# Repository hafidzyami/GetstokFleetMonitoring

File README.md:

# Tugas Akhir - Getstok Fleet Monitoring

Welcome to the **Getstok Fleet Monitoring** repository! This repository contains three main components: **Frontend**, **Backend**, and **Firmware**, each designed to work together seamlessly. Below are the details of each component.

---

## Table of Contents
- [Frontend](#frontend)
- [Backend](#backend)
- [Firmware](#firmware)
- [Setup](#setup)
  - [Frontend Setup](#frontend-setup)
  - [Backend Setup](#backend-setup)
  - [Firmware Setup](#firmware-setup)
- [License](#license)
- [Contributing](#contributing)

---

## Frontend

The **Frontend** is built using [Next.js](https://nextjs.org/), a React framework for server-rendered and statically generated web applications.

### Features
- Modern UI built with React and Next.js.
- Server-side rendering and API routes for efficient data fetching.
- Optimized performance and SEO.

---

# Backend - Getstok Fleet Monitoring

The backend for Getstok Fleet Monitoring is built with Go (Golang), using the GoFiber framework and GORM for database operations. It follows a clean n-tier architecture and provides RESTful API endpoints with authentication and role-based access control.

## Features

- **Authentication System**: Secure JWT-based authentication with roles (management, planner, driver)
- **RESTful API**: Clean API design following Google JSON Style Guide
- **Documentation**: Integrated Swagger API documentation
- **Database**: PostgreSQL integration with GORM
- **Docker Support**: Containerized development and production environments

## Tech Stack

- **Language**: Go 1.20+
- **Framework**: GoFiber v2
- **ORM**: GORM with PostgreSQL driver
- **Authentication**: JWT (JSON Web Tokens)
- **Documentation**: Swagger/OpenAPI
- **Containerization**: Docker & Docker Compose

## Project Structure

```
backend/
├── config/            # Configuration and database setup
├── controller/        # HTTP request handlers
├── docs/              # Swagger documentation
├── middleware/        # Middleware components (auth, logging, etc.)
├── model/             # Data models and DTOs
├── repository/        # Database access layer
├── service/           # Business logic
├── util/              # Utility functions
├── .env               # Environment variables (not in git)
├── .env.db            # Database environment variables (not in git)
├── .env.example       # Example environment variables
├── .env.db.example    # Example database environment variables
├── Dockerfile         # Multi-stage build for dev and prod
├── docker-compose.yml # Docker Compose configuration
├── go.mod             # Go modules
├── go.sum             # Dependencies lockfile
└── main.go            # Application entry point
```

## Environment Setup

### Prerequisites

- Go 1.20 or higher
- Docker and Docker Compose
- PostgreSQL (if not using Docker)

### Environment Variables

Two environment files are required:

1. `.env` - Application configuration:
```
DB_HOST=postgres
DB_PORT=5432
DB_USER=username
DB_PASSWORD=password
DB_NAME=getstok
DB_DRIVER=postgres
JWT_SECRET=your_secret_key
PORT=8080
```

2. `.env.db` - Database configuration:
```
POSTGRES_USER=username
POSTGRES_PASSWORD=password
POSTGRES_DB=getstok
```

Copy the example files and adjust as needed:
```bash
cp .env.example .env
cp .env.db.example .env.db
```

## Docker Setup

### Running with Docker

```bash
# Build and run containers
docker-compose up --build

# Run in background
docker-compose up -d

# View logs
docker-compose logs -f api
```

### Stopping Containers

```bash
# Stop and remove containers
docker-compose down
```

## Local Setup (Without Docker)

If you prefer to run the application locally:

1. Ensure PostgreSQL is running and accessible
2. Configure `.env` with your database connection details
3. Run the application:

```bash
# Get dependencies
go mod tidy

# Run the application
go run main.go
```

## API Documentation

The API documentation is available through Swagger UI when the application is running:

- Local: http://localhost:8080/swagger/index.html
- Production: https://your-api-domain.com/swagger/index.html

## Authentication

The API uses JWT tokens for authentication. Most endpoints require authentication and some are restricted by role.

### Available Roles

- `management`: Can register users and access all features
- `planner`: Can plan routes and manage fleet operations
- `driver`: Can view assigned routes and update status

### Authentication Flow

1. Register (Management only): `POST /api/auth/register`
2. Login: `POST /api/auth/login`
3. Use the returned token in the Authorization header: `Bearer <token>`

## Development

### Generating Swagger Documentation

```bash
# Install swag if not already installed
go install github.com/swaggo/swag/cmd/swag@latest

# Generate documentation
swag init -g main.go --output docs
```

### Database Migrations

Database migrations are handled automatically by GORM when the application starts.

## Contributing

1. Fork the repository
2. Create your feature branch (`git checkout -b feature/amazing-feature`)
3. Commit your changes (`git commit -m 'Add some amazing feature'`)
4. Push to the branch (`git push origin feature/amazing-feature`)
5. Open a Pull Request

---

## Firmware

The **Firmware** is written in **C++** to control hardware devices efficiently.

### Features
- Optimized for resource-constrained environments.
- Compatible with a variety of microcontrollers.
- Includes communication protocols for interacting with the backend.

---

## Setup

```yaml
frontend:
  steps:
    - navigate: "cd frontend"
    - install_dependencies: "npm install"
    - run_development_server: "npm run dev"
    - open_browser: "http://localhost:3000"

backend:
  steps:
    - navigate: "cd backend"
    - initialize_modules: "go mod tidy"
    - run_application: "go run cmd/main.go"
    - api_url: "http://localhost:8080"

firmware:
  steps:
    - navigate: "cd firmware"
    - open_project: "Open the project in PlatformIO"
    - build_project: "Use the 'Build' button in PlatformIO"
    - upload_firmware: "Use the 'Upload' button to flash the microcontroller"

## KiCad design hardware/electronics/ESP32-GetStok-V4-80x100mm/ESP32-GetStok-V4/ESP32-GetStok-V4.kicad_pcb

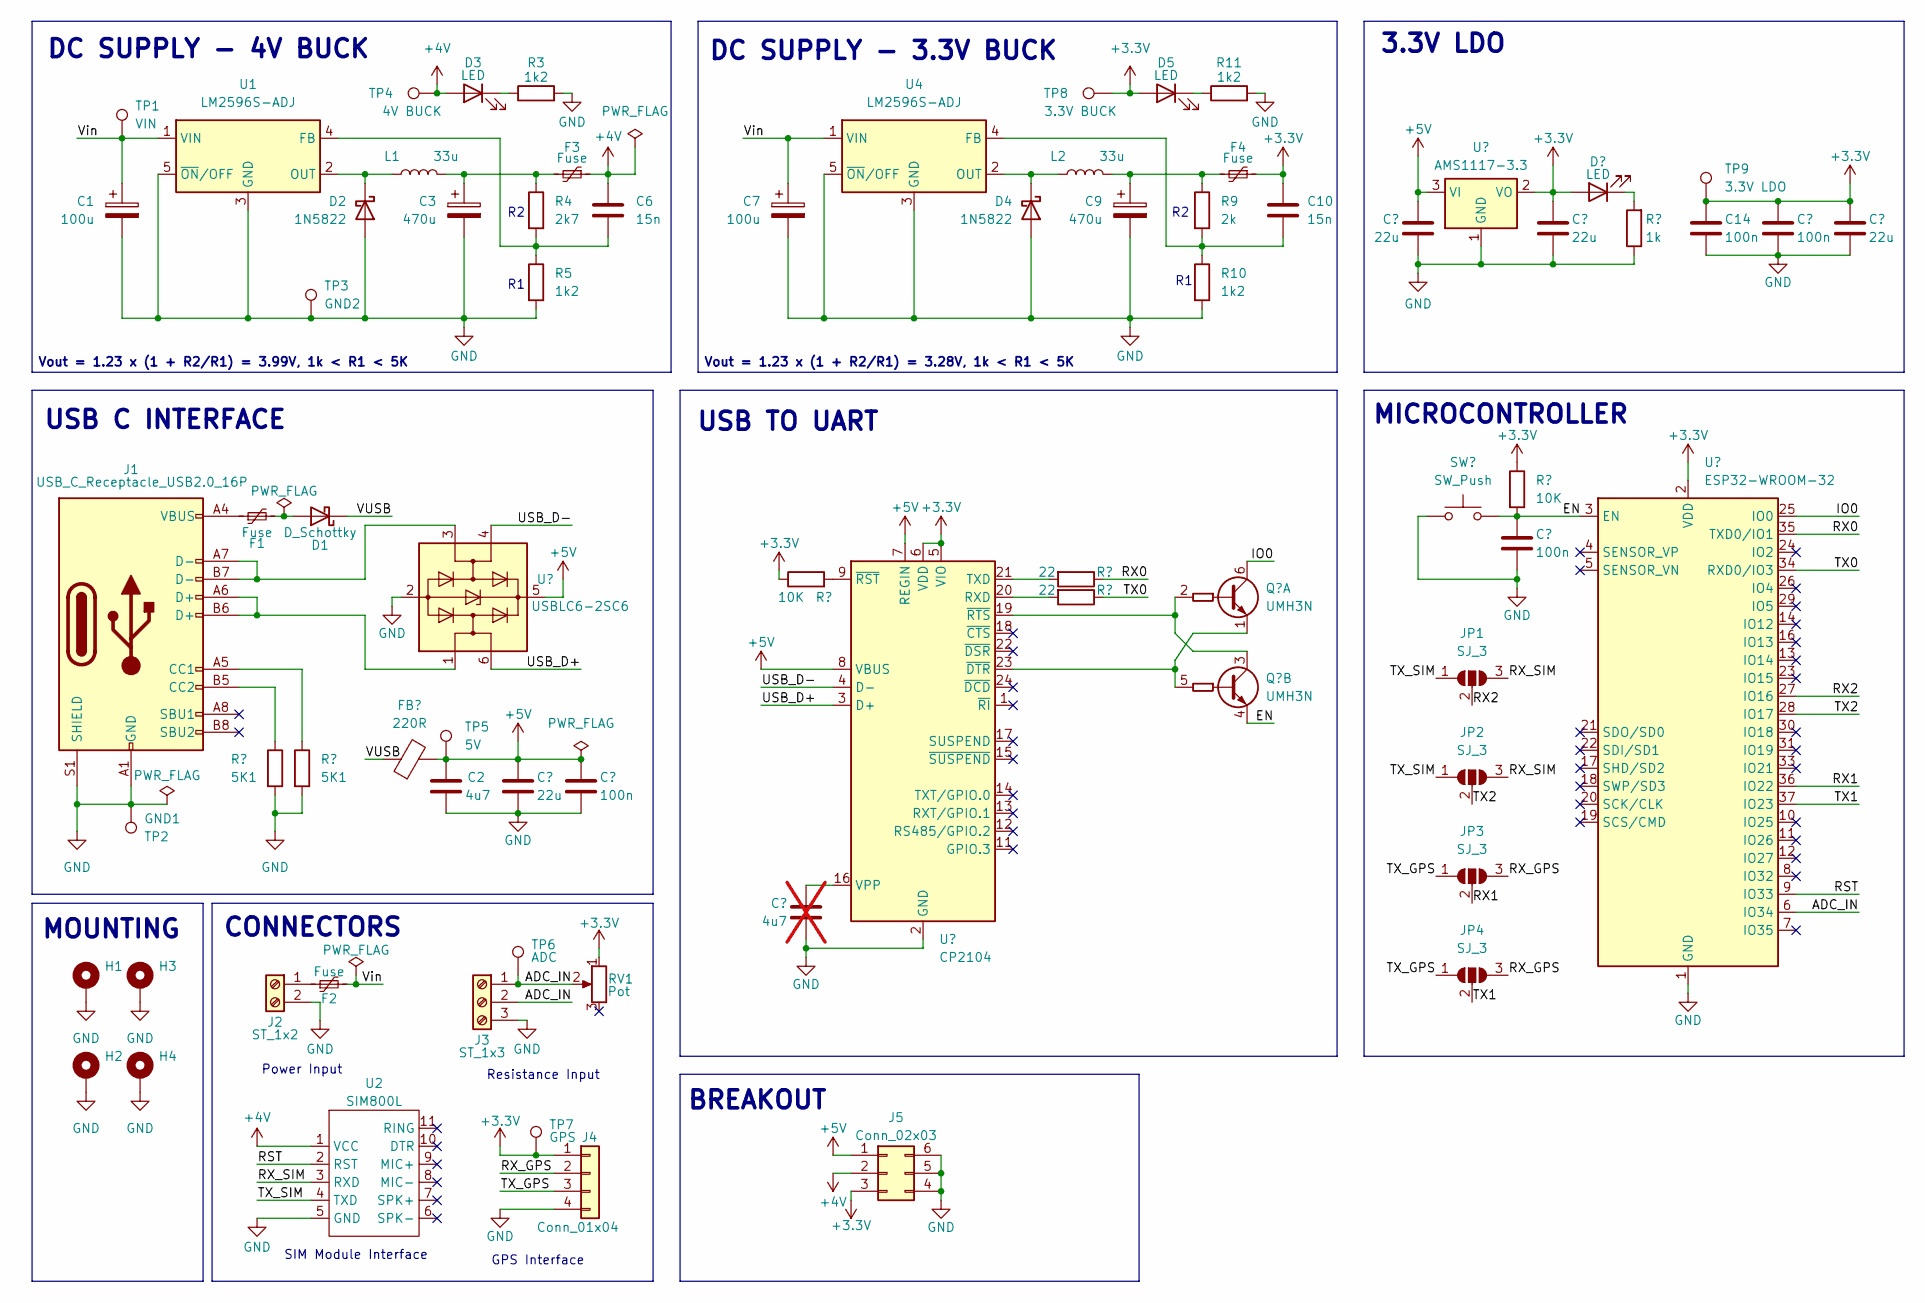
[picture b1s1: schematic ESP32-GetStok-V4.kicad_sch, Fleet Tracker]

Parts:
C1, C7: 100u; CP_Elec_5x5.4; JLCPCB Part # C3001205
C2: 4u7; C_0805_2012Metric; JLCPCB Part # C2918490
C3, C9: 470u; CP_Elec_6.3x7.7; JLCPCB Part # C18203156
C4, C11, C13, C16: 22u; C_0805_2012Metric; JLCPCB Part # C129302
C5, C12, C14, C15: 100n; C_0805_2012Metric; JLCPCB Part # C49678
C6, C10: 15n; C_0805_2012Metric; JLCPCB Part # C445728
C8: 4u7; C_0805_2012Metric; JLCPCB Part # C2918490; not fitted
D1: D_Schottky; D_SMA; JLCPCB Part # C727058
D2, D4: 1N5822; D_DO-201AD_P15.24mm_Horizontal; JLCPCB Part # C84619
D3, D5, D6: LED; LED_0805_2012Metric; JLCPCB Part # C516809
F1, F2, F3, F4: Fuse; Fuse_1206_3216Metric; JLCPCB Part # C2982271
FB1: 220R; L_0805_2012Metric; JLCPCB Part # C85840
H1, H2, H3, H4: MountingHole_Pad; MountingHole_5mm_Pad
J1: USB_C_Receptacle_USB2.0_16P; USB_C_Receptacle_HRO_TYPE-C-31-M-12; JLCPCB Part # C165948
J2: ST_1x2; TerminalBlock_Phoenix_PT-1,5-2-5.0-H_1x02_P5.00mm_Horizontal
J3: ST_1x3; TerminalBlock_Phoenix_PT-1,5-3-5.0-H_1x03_P5.00mm_Horizontal
J4: Conn_01x04; PinSocket_1x04_P2.54mm_Vertical; JLCPCB Part # C2718488
J5: Conn_02x03; PinSocket_2x03_P2.54mm_Vertical; JLCPCB Part # C2897404
JP1, JP2, JP3, JP4: SJ_3; SolderJumper-3_P1.3mm_Open_Pad1.0x1.5mm
L1, L2: 33u; L_12x12mm_H8mm; JLCPCB Part # C167264
Q1: UMH3N; SOT-363_SC-70-6; JLCPCB Part # C20611976
R1, R2: 5K1; R_0805_2012Metric; JLCPCB Part # C2988915
R3, R5, R10, R11: 1k2; R_0805_2012Metric; JLCPCB Part # C2765921
R4: 2k7; R_0805_2012Metric; JLCPCB Part # C114520
R6, R12: 10K; R_0805_2012Metric; JLCPCB Part # C84376
R7, R8: 22; R_0805_2012Metric; JLCPCB Part # C416949
R9: 2k; R_0805_2012Metric; JLCPCB Part # C2765638
R13: 1k; R_0805_2012Metric; JLCPCB Part # C856765
RV1: Pot; Potentiometer_Bourns_3296W_Vertical; JLCPCB Part # C57089
SW1: SW_Push; SW_Tactile_SPST_NO_Straight_CK_PTS636Sx25SMTRLFS; JLCPCB Part # C318938
TP1: VIN; TestPoint_Pad_D1.5mm
TP2: GND1; TestPoint_Pad_D1.5mm
TP3: GND2; TestPoint_Pad_D1.5mm
TP4: 4V BUCK; TestPoint_Pad_D1.5mm
TP5: 5V; TestPoint_Pad_D1.5mm
TP6: ADC; TestPoint_Pad_D1.5mm
TP7: GPS; TestPoint_Pad_D1.5mm
TP8: 3.3V BUCK; TestPoint_Pad_D1.5mm
TP9: 3.3V LDO; TestPoint_Pad_D1.5mm
U1, U4: LM2596S-ADJ; TO-263-5_TabPin3; JLCPCB Part # C7419982
U2: SIM800L
U3: USBLC6-2SC6; SOT-23-6; JLCPCB Part # C2827654
U5: CP2104; QFN-24-1EP_4x4mm_P0.5mm_EP2.6x2.6mm; JLCPCB Part # C47742
U6: AMS1117-3.3; SOT-223-3_TabPin2; JLCPCB Part # C347222
U7: ESP32-WROOM-32; JLCPCB Part # C82899

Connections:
+3.3V: C10.1, C13.1, C14.1, C15.1, C16.1, D5.2 (A), D6.2 (A), F4.1, J4.1, J5.3, R6.1, R12.1, RV1.1, TP7.1, TP8.1, TP9.1, U5.5 (VIO), U5.6 (VDD), U6.2 (VO), U7.2 (VDD)
+4V: C6.1, D3.2 (A), F3.1, J5.2, TP4.1, U2.1 (VCC)
+5V: C2.2, C4.1, C5.1, C11.1, FB1.2, J5.1, TP5.1, U3.5 (VBUS), U5.7 (REGIN), U5.8 (VBUS), U6.3 (VI)
/ADC_IN: J3.1, J3.2, RV1.2, TP6.1, U7.6 (IO34)
/EN: C12.1, Q1.4 (E2), R12.2, SW1.2, U7.3 (EN)
/IO0: Q1.6 (C1), U7.25 (IO0)
/RST: U2.2 (RST), U7.9 (IO33)
/RX0: R7.1, U7.35 (TXD0/IO1)
/RX1: JP3.2 (C), U7.36 (IO22)
/RX2: JP1.2 (C), U7.27 (IO16)
/RX_GPS: J4.2, JP3.3 (B), JP4.3 (B)
/RX_SIM: JP1.3 (B), JP2.3 (B), U2.3 (RXD)
/TX0: R8.1, U7.34 (RXD0/IO3)
/TX1: JP4.2 (C), U7.37 (IO23)
/TX2: JP2.2 (C), U7.28 (IO17)
/TX_GPS: J4.3, JP3.1 (A), JP4.1 (A)
/TX_SIM: JP1.1 (A), JP2.1 (A), U2.4 (TXD)
/USB_D+: U3.6 (I/O1), U5.3 (D+)
/USB_D-: U3.4 (I/O2), U5.4 (D-)
/VUSB: D1.1 (K), FB1.1
/Vin: C1.1, C7.1, F2.2, TP1.1, U1.1 (VIN), U4.1 (VIN)
GND: C1.2, C2.1, C3.2, C4.2, C5.2, C7.2, C8.2, C9.2, C11.2, C12.2, C13.2, C14.2, C15.2, C16.2, D2.2 (A), D4.2 (A), H1.1, H2.1, H3.1, H4.1, J1.A1 (GND), J1.A12 (GND), J1.B1 (GND), J1.B12 (GND), J1.S1 (SHIELD), J2.2, J3.3, J4.4, J5.4, J5.5, J5.6, R1.2, R2.2, R3.2, R5.2, R10.2, R11.2, R13.1, SW1.1, TP2.1, TP3.1, U1.3 (GND), U1.5 (~ON/OFF), U2.5 (GND), U3.2 (GND), U4.3 (GND), U4.5 (~ON/OFF), U5.2 (GND), U5.25 (GND), U6.1 (GND), U7.1 (GND), U7.15 (GND), U7.38 (GND), U7.39 (GND)
unnamed: C3.1, F3.2, L1.2, R4.1
unnamed: C9.1, F4.2, L2.2, R9.1
unnamed: D1.2 (A), F1.2
unnamed: D2.1 (K), L1.1, U1.2 (OUT)
unnamed: D3.1 (K), R3.1
unnamed: D4.1 (K), L2.1, U4.2 (OUT)
unnamed: D5.1 (K), R11.1
unnamed: D6.1 (K), R13.2
unnamed: F1.1, J1.A4 (VBUS), J1.A9 (VBUS), J1.B4 (VBUS), J1.B9 (VBUS)
unnamed: J1.A5 (CC1), R2.1
unnamed: J1.B5 (CC2), R1.1
unnamed: J1.A6 (D+), J1.B6 (D+), U3.1 (I/O1)
unnamed: J1.A7 (D-), J1.B7 (D-), U3.3 (I/O2)
unnamed: F2.1, J2.1
unnamed: Q1.2 (B1), Q1.3 (C2), U5.19 (~RTS)
unnamed: Q1.1 (E1), Q1.5 (B2), U5.23 (~DTR)
unnamed: C6.2, R4.2, R5.1, U1.4 (FB)
unnamed: C10.2, R9.2, R10.1, U4.4 (FB)
unnamed: R8.2, U5.20 (RXD)
unnamed: R7.2, U5.21 (TXD)
unnamed: C8.1, U5.16 (VPP)
unnamed: R6.2, U5.9 (~RST)

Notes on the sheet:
CONNECTORS
DC SUPPLY - 3.3V BUCK
Vout = 1.23 x (1 + R2/R1) = 3.28V, 1k < R1 < 5K
USB C INTERFACE
Power Input
SIM Module Interface
BREAKOUT
Resistance Input
3.3V LDO
GPS Interface
MICROCONTROLLER
USB TO UART
Vout = 1.23 x (1 + R2/R1) = 3.99V, 1k < R1 < 5K
MOUNTING
DC SUPPLY - 4V BUCK

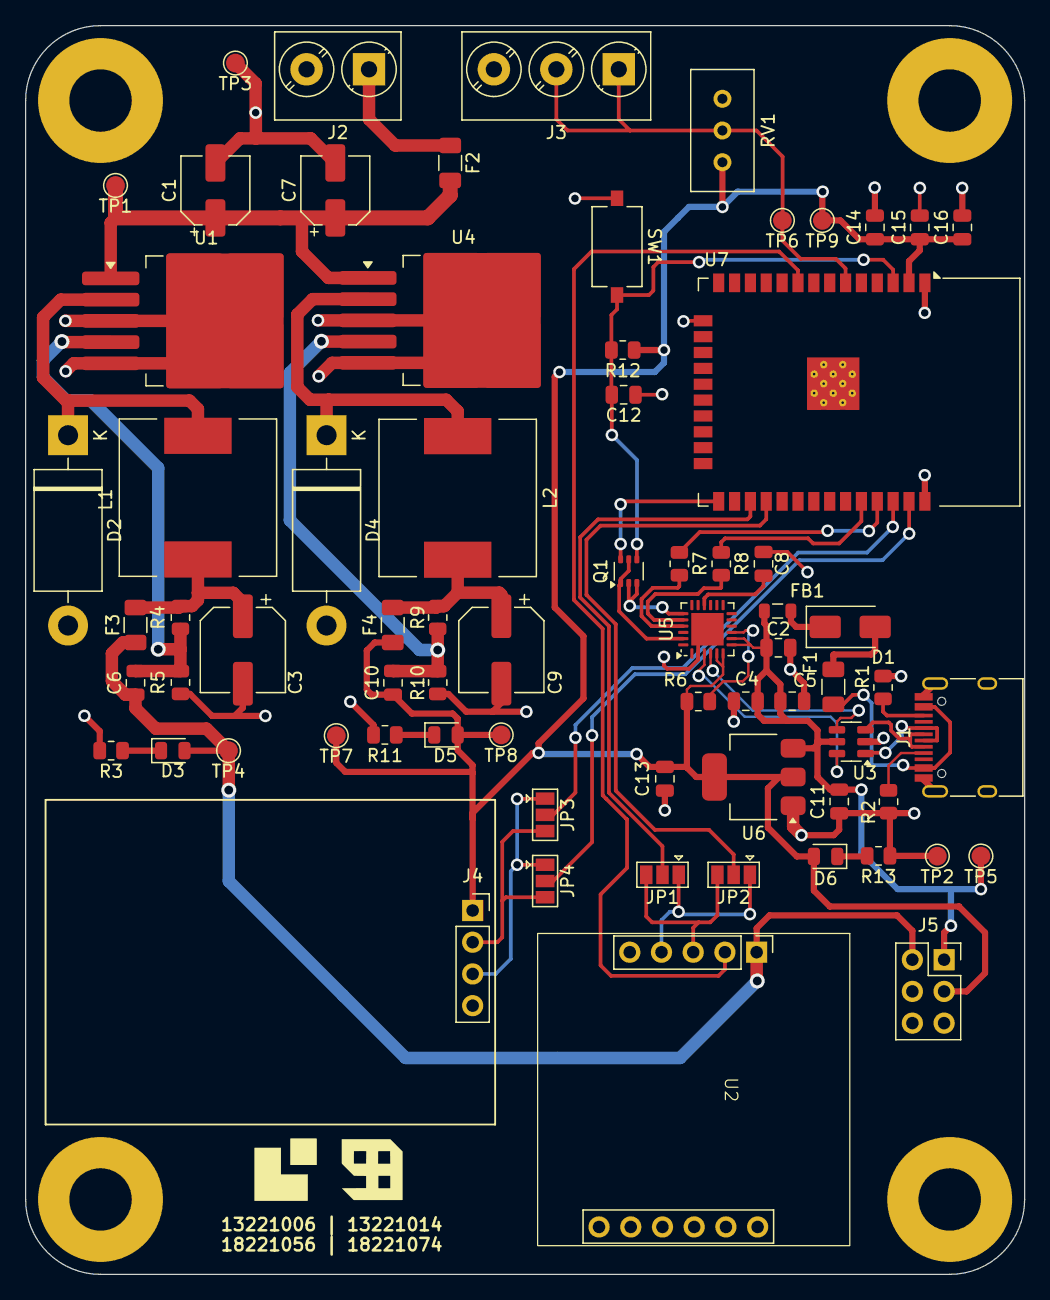
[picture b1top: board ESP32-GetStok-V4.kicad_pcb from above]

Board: 2 copper layers, 80.0 x 100.0 mm, 74 parts (0 on the bottom side), 44 nets.

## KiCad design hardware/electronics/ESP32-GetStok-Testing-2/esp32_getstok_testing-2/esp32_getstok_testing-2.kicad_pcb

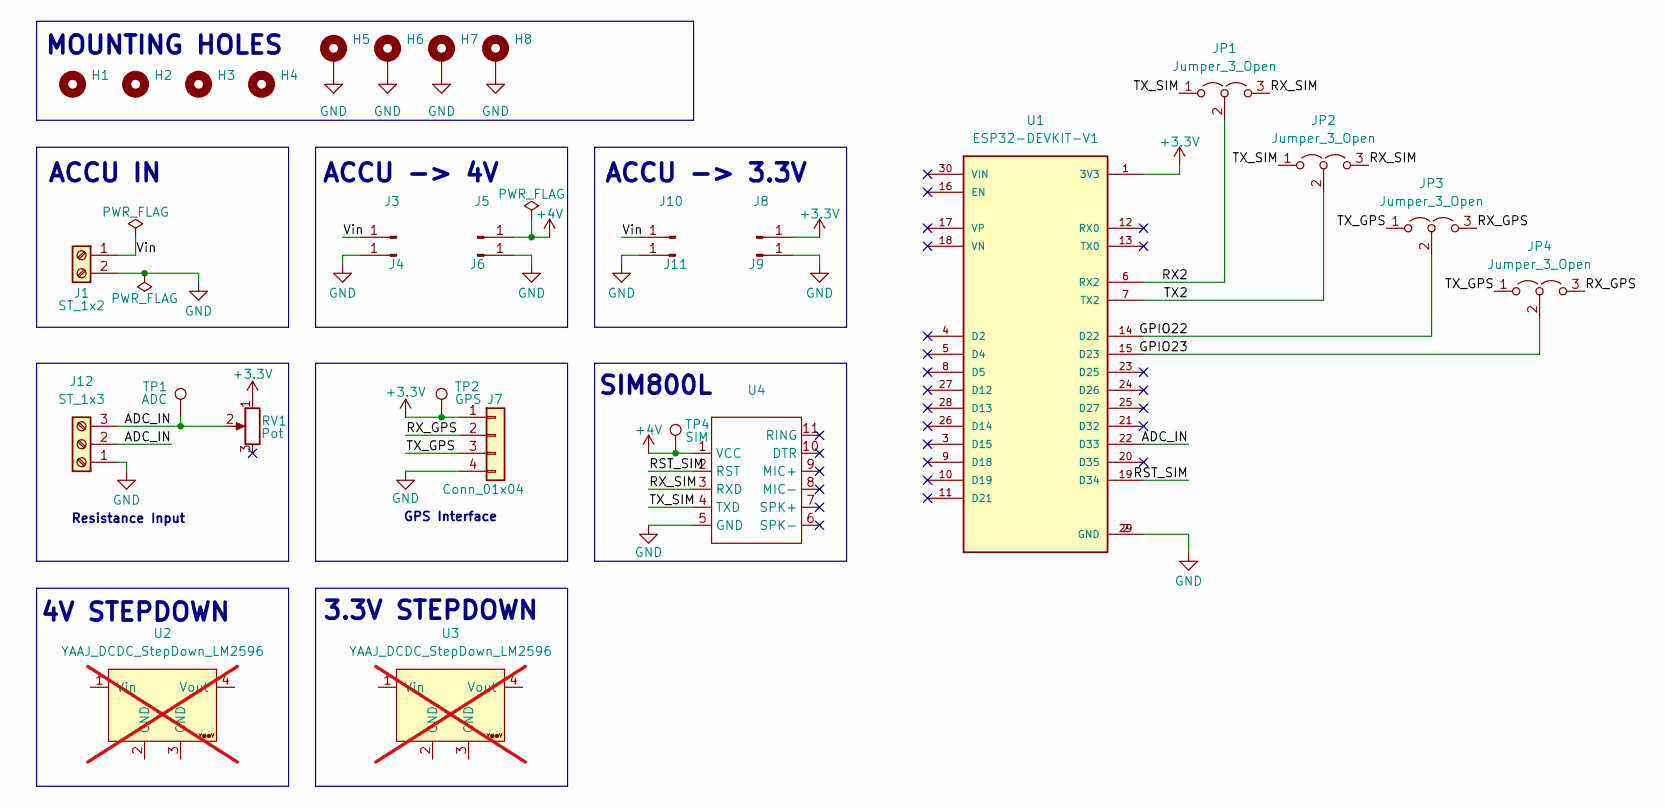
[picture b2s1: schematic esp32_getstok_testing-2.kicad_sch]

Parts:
H1, H2, H3, H4: MountingHole; MountingHole_3.2mm_M3
H5, H6, H7, H8: MountingHole_Pad; MountingHole_5mm_Pad
J1: ST_1x2; TerminalBlock_Phoenix_PT-1,5-2-5.0-H_1x02_P5.00mm_Horizontal
J3, J4, J5, J6, J8, J9, J10, J11: Conn_01x01; PinHeader_1x01_P2.54mm_Vertical
J7: Conn_01x04; PinSocket_1x04_P2.54mm_Vertical
J12: ST_1x3; TerminalBlock_Phoenix_PT-1,5-3-5.0-H_1x03_P5.00mm_Horizontal
JP1, JP2, JP3, JP4: Jumper_3_Open; SolderJumper-3_P1.3mm_Open_Pad1.0x1.5mm
RV1: Pot; Potentiometer_Bourns_3296W_Vertical
TP1: ADC; TestPoint_Pad_D1.5mm
TP2: GPS; TestPoint_Pad_D1.5mm
TP4: SIM; TestPoint_Pad_D1.5mm
U1: ESP32-DEVKIT-V1; MODULE_ESP32_DEVKIT_V1; PARTREV N/A
U2, U3: YAAJ_DCDC_StepDown_LM2596; not fitted
U4: SIM800L

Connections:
+3.3V: J7.1, J8.1, RV1.1, TP2.1, U1.1 (3V3)
+4V: J5.1, TP4.1, U4.1 (VCC)
/ADC_IN: J12.2, J12.3, RV1.2, TP1.1, U1.22 (D33)
/GPIO22: JP3.2 (C), U1.14 (D22)
/GPIO23: JP4.2 (C), U1.15 (D23)
/RST_SIM: U1.19 (D34), U4.2 (RST)
/RX2: JP1.2 (C), U1.6 (RX2)
/RX_GPS: J7.2, JP3.3 (B), JP4.3 (B)
/RX_SIM: JP1.3 (B), JP2.3 (B), U4.3 (RXD)
/TX2: JP2.2 (C), U1.7 (TX2)
/TX_GPS: J7.3, JP3.1 (A), JP4.1 (A)
/TX_SIM: JP1.1 (A), JP2.1 (A), U4.4 (TXD)
/Vin: J1.1, J3.1, J10.1
GND: H5.1, H6.1, H7.1, H8.1, J1.2, J4.1, J6.1, J7.4, J9.1, J11.1, J12.1, U1.2 (GND), U1.29 (GND), U4.5 (GND)

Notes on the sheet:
ACCU -> 3.3V
ACCU -> 4V
4V STEPDOWN
MOUNTING HOLES
ACCU IN
Resistance Input
SIM800L
3.3V STEPDOWN
GPS Interface

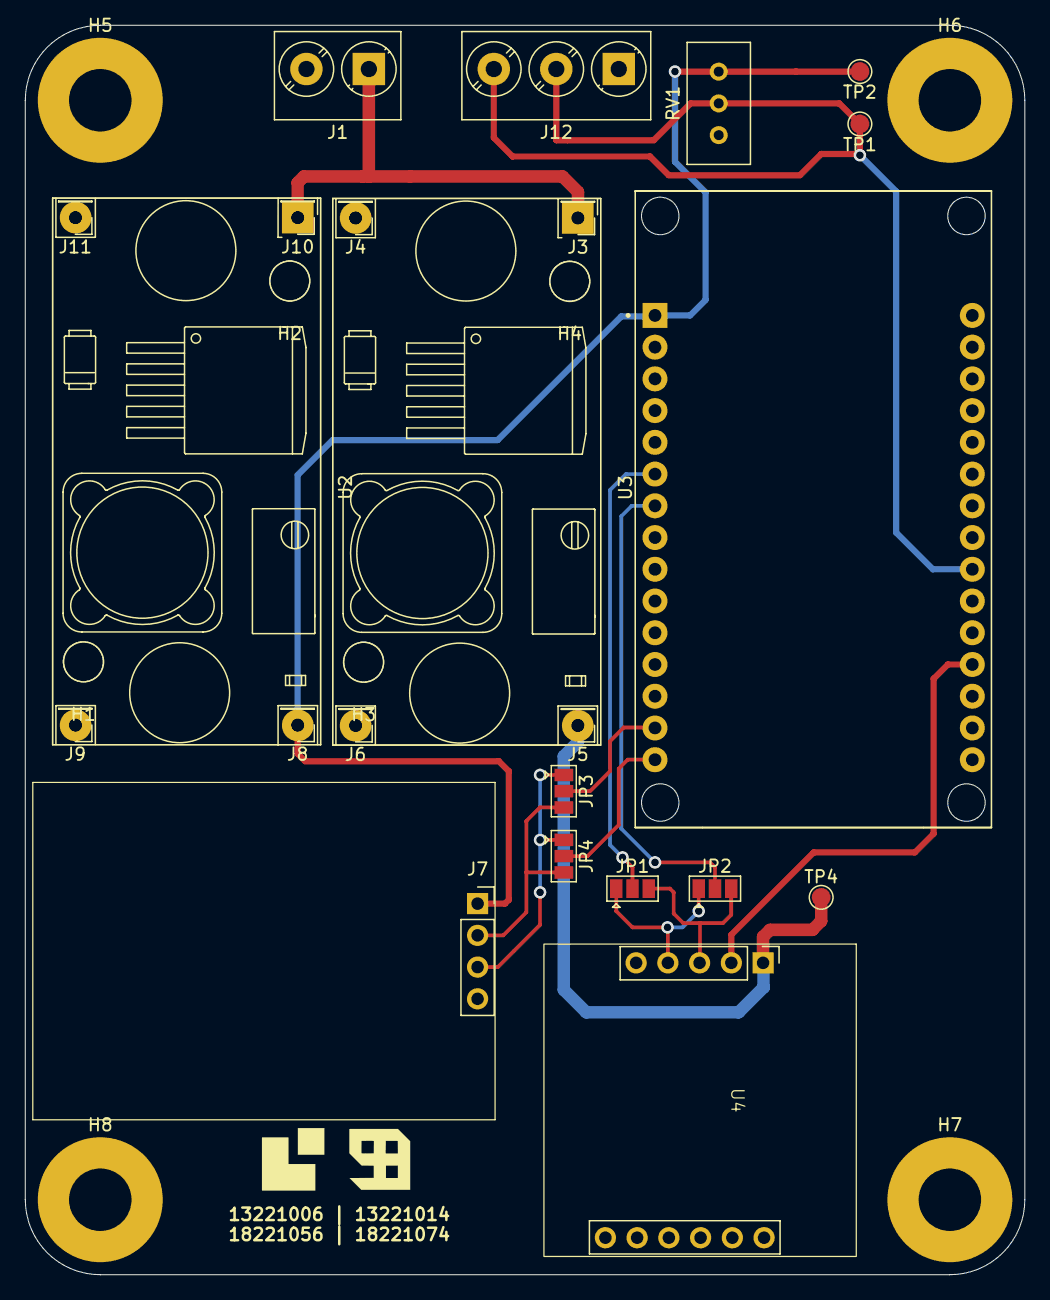
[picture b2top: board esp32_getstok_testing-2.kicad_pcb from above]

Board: 2 copper layers, 80.0 x 100.0 mm, 31 parts (0 on the bottom side), 14 nets.

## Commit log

2025-01-11 init firmware and backend
2025-01-11 add raw readme
2025-01-13 routing
2025-01-13 add impassible route algorithm
2025-01-13 add extra info toll
2025-01-14 fix remove markers
2025-01-15 revisi page awal
2025-03-11 init backend with auth api
2025-03-13 add routingservice and elevation
2025-03-14 remove .env hehe
2025-03-14 add gitignore
2025-03-14 add auth and documentation
2025-03-15 add auth and adjust backend api
2025-03-15 backend push notification
2025-03-19 add notification
2025-03-29 remove proxy
2025-03-30 add notification service
2025-04-03 add docker compose for fe
2025-04-03 add docker to notification service
2025-04-04 add github actions
2025-04-04 fix docker-compose yml
2025-04-04 fix dockercompose for notif
2025-04-04 add tailwindcss to prod
2025-04-05 fix css
2025-04-05 add no cache for github actions docker build
2025-04-05 fix eslint to github actions
2025-04-05 change ip address be and notif
2025-04-05 add user seed and reroute notif service
2025-04-05 fix env for notification service
2025-04-05 add eslint ignore, fix eslint, add config for dev and prod scenario
2025-04-05 fix eslint
2025-04-05 fix eslint final
2025-04-06 add mqtt broker to ec2
2025-04-06 slicing figma
2025-04-06 adjust
2025-04-06 add github action for staging
2025-04-06 update github action
2025-04-06 update github action for staging
2025-04-06 final fix github action
2025-04-06 semoga bisa
2025-04-06 fix eslint and github action
2025-04-06 capek
2025-04-06 update package json
2025-04-06 check env
2025-04-07 fix daftar user
2025-04-07 update github action to prune docker first
2025-04-07 add mqtt broker
2025-04-10 add keep alive to ssh
2025-04-10 add truck fuel and position endpoint
2025-04-10 fix github action for staging
2025-04-10 fix GA yml
2025-04-10 fix deploy staging
2025-04-10 add websocket
2025-04-13 fleet monitoring
2025-04-13 add timezone
2025-04-14 add routing endpoint
2025-04-14 fix color in planrouting
2025-04-14 fix icon
2025-04-15 lupa apa aja
2025-04-15 fix error
2025-04-15 fix type error
2025-04-15 add fetch driver and truck
2025-04-15 fix deploy.yml
2025-04-15 fix next build
2025-04-16 Add Hardware and Firmware
2025-04-16 update githubaction
2025-04-16 add feature and fix websocket
2025-04-17 add s3 service
2025-04-17 add driver route list
2025-04-17 pusing
2025-04-17 gatau capek
2025-04-18 add avoidance area
2025-04-19 dashboard
2025-04-19 dockerhub
2025-04-19 dockerhub2
2025-04-19 last
2025-04-19 ganti jadi latest
2025-04-19 update github action for main
2025-04-21 -2mil line
2025-04-21 hapus electronics
2025-04-22 update swagger
2025-04-22 swag
2025-04-22 ganti
2025-04-25 feat: add responsive mobile & desktop
2025-04-26 deviasi rute
2025-04-26 DEVIASI
2025-04-26 update deviasi rute
2025-04-26 add last 30 days of fuel and position history endpoint api
2025-04-28 add deviation table in db
2025-04-28 initialize db notif
2025-05-04 fixing
2025-05-05 fixing linting
2025-05-06 add deviation from being deleted
2025-05-06 fix linting backend
2025-05-06 fix linting go
2025-05-14 fix: show deteksi kuantitas OCR
2025-05-14 feat: add receipt
2025-05-14 increase limit pagination
2025-05-16 feat: add ocr
2025-05-16 fix ocr
2025-05-16 fuel sensor graph
2025-05-17 add 30 days of fuel and receipt, and not dummy anymore
2025-05-17 update but stiill error for the chart
2025-05-17 fix glitch when rendering chart
2025-05-17 add truck idle detection
2025-05-17 add idle notification in frontend
2025-05-18 gps tab
2025-05-18 done
2025-05-18 update 1 year expired image
2025-05-19 add k6 load testing with prometheus grafana influxdb
2025-05-19 fix dashboard
2025-05-20 testing
2025-05-20 k6 and monitoring for ec2
2025-05-20 update sh
2025-05-20 update dot env example
2025-05-22 fix backend linting and add warning to ocr
2025-05-27 feat(planner): ganti generate button text "kirim rute" & buat rute dahulu sebelum kirim rute
2025-05-27 feat: ganti role "user" sesuai dengan role current login user
2025-05-27 fix(driver): menampilkan icon pada table
2025-05-27 fix(management): map, tab data, overlap zoom in/out
2025-05-27 fix(management): gap user, truct list
2025-05-31 focus on 1 truck in today gps tabs
2025-05-31 test
2025-05-31 add polyline position for "today" in gps tab
2025-06-06 change subscribe topic and add notification for idle
2025-06-09 change payload received for mqtt
2025-06-09 fix mqtt payload in backend
2025-06-10 adjust timezone
2025-06-12 adjust timezone for wib realtime update
2025-06-19 fix metrics error
2025-06-20 fix error prometheus after several hours
2025-06-20 fix prometheus
2025-06-23 fix chart
